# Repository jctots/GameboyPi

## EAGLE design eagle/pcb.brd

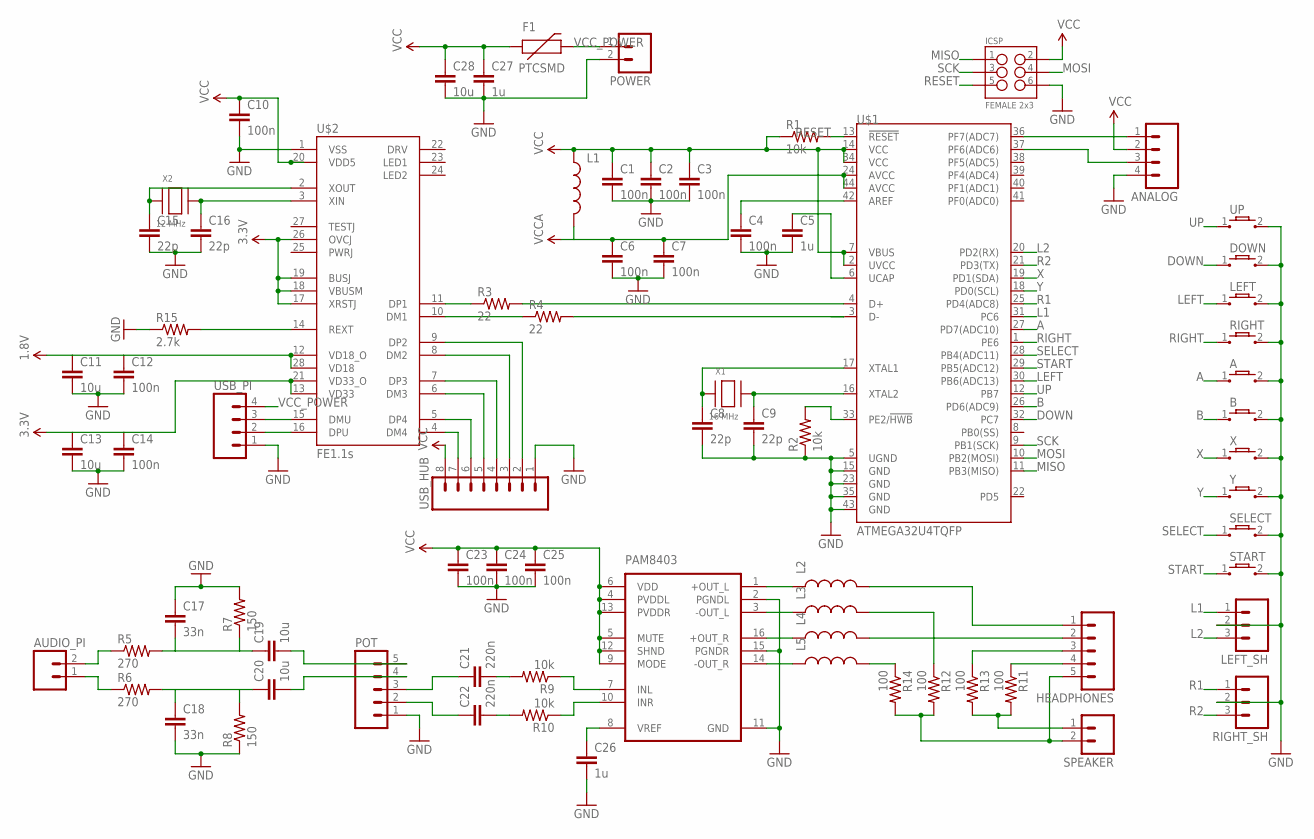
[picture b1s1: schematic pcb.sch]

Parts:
A: DMG_CONDUCTIVE; CIRCLE_BUTTON2
ANALOG: M04PTH; 1X04
AUDIO_PI: M02PTH; 1X02
B: DMG_CONDUCTIVE; CIRCLE_BUTTON2
C1, C2, C3, C4, C6, C7, C10, C12, C14, C23, C24, C25: 100n; 0805
C5, C26, C27: 1u; 0805
C8, C9, C15, C16: 22p; 0805
C11, C13, C19, C20, C28: 10u; 0805
C17, C18: 33n; 0805
C21, C22: 220n; 0805
DOWN: DMG_CONDUCTIVE; CIRCLE_BUTTON2
F1: PTCSMD; PTC-1206
HEADPHONES: M05PTH; 1X05
ICSP: FEMALE 2x3; 2X3
L1, L2, L3, L4, L5: INDUCTOR0805; 0805
LEFT: DMG_CONDUCTIVE; CIRCLE_BUTTON2
LEFT_SH: M03PTH; 1X03
PAM8403: PAM8403; SOP-16
POT: M05PTH; 1X05
POWER: M02PTH; 1X02
R1, R2, R9, R10: 10k; 0805
R3, R4: 22; 0805
R5, R6: 270; 0805
R7, R8: 150; 0805
R11, R12, R13, R14: 100; 0805
R15: 2.7k; 0805
RIGHT: DMG_CONDUCTIVE; CIRCLE_BUTTON2
RIGHT_SH: M03PTH; 1X03
SELECT: DMG_CONDUCTIVE2; START_STOP2
SPEAKER: M02PTH; 1X02
START: DMG_CONDUCTIVE2; START_STOP2
U$1: ATMEGA32U4TQFP; SPARKFUN-DIGITALIC_TQFP44
U$2: FE1.1S; FE1.1S_SSOP-28
UP: DMG_CONDUCTIVE; CIRCLE_BUTTON2
USB_HUB: M08; 1X08_ROUND
USB_PI: M04PTH; 1X04
X: DMG_CONDUCTIVE; CIRCLE_BUTTON2
X1: 16 MHz; NX5032
X2: 12 MHz; NX5032
Y: DMG_CONDUCTIVE; CIRCLE_BUTTON2

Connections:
1.8V: C11.1, C12.1, U$2.12 (VD18_O), U$2.28 (VD18)
3.3V: C13.1, C14.1, U$2.13 (VD33), U$2.17 (XRSTJ), U$2.18 (VBUSM), U$2.19 (BUSJ), U$2.21 (VD33_O), U$2.26 (OVCJ)
A: A.1, U$1.27 (PD7(ADC10))
AUDIO_GND: HEADPHONES.5, R12.2, R14.2, SPEAKER.2
AUDIO_L2MONO: HEADPHONES.4, R11.1
AUDIO_MONO: R11.2, R13.2, SPEAKER.1
AUDIO_R2MONO: HEADPHONES.3, R13.1
AUDIO_STEREO_L: HEADPHONES.1, L2.2
AUDIO_STEREO_R: HEADPHONES.2, L4.2
B: B.1, U$1.26 (PD6(ADC9))
DOWN: DOWN.1, U$1.32 (PC7)
GND: A.2, ANALOG.4, B.2, C1.2, C2.2, C3.2, C4.2, C5.2, C6.2, C7.2, C8.2, C9.2, C10.2, C11.2, C12.2, C13.2, C14.2, C15.2, C16.2, C17.1, C18.2, C23.2, C24.2, C25.2, C26.2, C27.2, C28.2, DOWN.2, ICSP.6, LEFT.2, LEFT_SH.2, PAM8403.2 (PGNDL), PAM8403.11 (GND), PAM8403.15 (PGNDR), POT.1, POWER.2, R2.1, R7.2, R8.1, R15.1, RIGHT.2, RIGHT_SH.2, SELECT.2, START.2, U$1.5 (UGND), U$1.15 (GND), U$1.23 (GND), U$1.35 (GND), U$1.43 (GND), U$2.1 (VSS), UP.2, USB_HUB.1, USB_PI.1, X.2, Y.2
L1: LEFT_SH.1, U$1.31 (PC6)
L2: LEFT_SH.3, U$1.20 (PD2(RX))
LEFT: LEFT.1, U$1.30 (PB6(ADC13))
MISO: ICSP.1, U$1.11 (PB3(MISO))
MOSI: ICSP.4, U$1.10 (PB2(MOSI))
unnamed: C4.1, U$1.42 (AREF)
unnamed: C5.1, U$1.6 (UCAP)
unnamed: R2.2, U$1.33 (PE2/!HWB)
unnamed: R3.1, U$2.11 (DP1)
unnamed: R4.1, U$2.10 (DM1)
unnamed: C8.1, U$1.17 (XTAL1), X1.P$1
unnamed: C9.1, U$1.16 (XTAL2), X1.P$2
unnamed: R3.2, U$1.4 (D+)
unnamed: R4.2, U$1.3 (D-)
unnamed: C15.1, U$2.2 (XOUT), X2.P$1
unnamed: C16.1, U$2.3 (XIN), X2.P$2
unnamed: AUDIO_PI.2, R5.1
unnamed: AUDIO_PI.1, R6.1
unnamed: C17.2, C19.1, R5.2, R7.1
unnamed: C18.1, C20.1, R6.2, R8.2
unnamed: C26.1, PAM8403.8 (VREF)
unnamed: L2.1, PAM8403.1 (+OUT_L)
unnamed: C19.2, POT.5
unnamed: C20.2, POT.4
unnamed: C21.1, POT.3
unnamed: C22.1, POT.2
unnamed: C21.2, R9.2
unnamed: C22.2, R10.2
unnamed: PAM8403.7 (INL), R9.1
unnamed: PAM8403.10 (INR), R10.1
unnamed: L3.1, PAM8403.3 (-OUT_L)
unnamed: L3.2, R12.1
unnamed: L4.1, PAM8403.16 (+OUT_R)
unnamed: L5.1, PAM8403.14 (-OUT_R)
unnamed: L5.2, R14.1
unnamed: U$2.4 (DM4), USB_HUB.7
unnamed: U$2.5 (DP4), USB_HUB.6
unnamed: U$2.6 (DM3), USB_HUB.5
unnamed: R15.2, U$2.14 (REXT)
unnamed: U$2.7 (DP3), USB_HUB.4
unnamed: U$2.8 (DM2), USB_HUB.3
unnamed: ANALOG.1, U$1.36 (PF7(ADC7))
unnamed: ANALOG.3, U$1.37 (PF6(ADC6))
unnamed: U$2.9 (DP2), USB_HUB.2
unnamed: U$2.15 (DMU), USB_PI.3
unnamed: U$2.16 (DPU), USB_PI.2
R1: RIGHT_SH.1, U$1.25 (PD4(ADC8))
R2: RIGHT_SH.3, U$1.21 (PD3(TX))
RESET: ICSP.5, R1.2, U$1.13 (!RESET)
RIGHT: RIGHT.1, U$1.1 (PE6)
SCK: ICSP.3, U$1.9 (PB1(SCK))
SELECT: SELECT.1, U$1.28 (PB4(ADC11))
START: START.1, U$1.29 (PB5(ADC12))
UP: U$1.12 (PB7), UP.1
VCC: ANALOG.2, C1.1, C2.1, C3.1, C10.1, C23.1, C24.1, C25.1, C27.1, C28.1, F1.1, ICSP.2, L1.1, PAM8403.4 (PVDDL), PAM8403.5 (MUTE), PAM8403.6 (VDD), PAM8403.9 (MODE), PAM8403.12 (SHND), PAM8403.13 (PVDDR), R1.1, U$1.2 (UVCC), U$1.7 (VBUS), U$1.14 (VCC), U$1.34 (VCC), U$2.20 (VDD5), USB_HUB.8
VCCA: C6.1, C7.1, L1.2, U$1.24 (AVCC), U$1.44 (AVCC)
VCC_POWER: F1.2, POWER.1, USB_PI.4
X: U$1.19 (PD1(SDA)), X.1
Y: U$1.18 (PD0(SCL)), Y.1

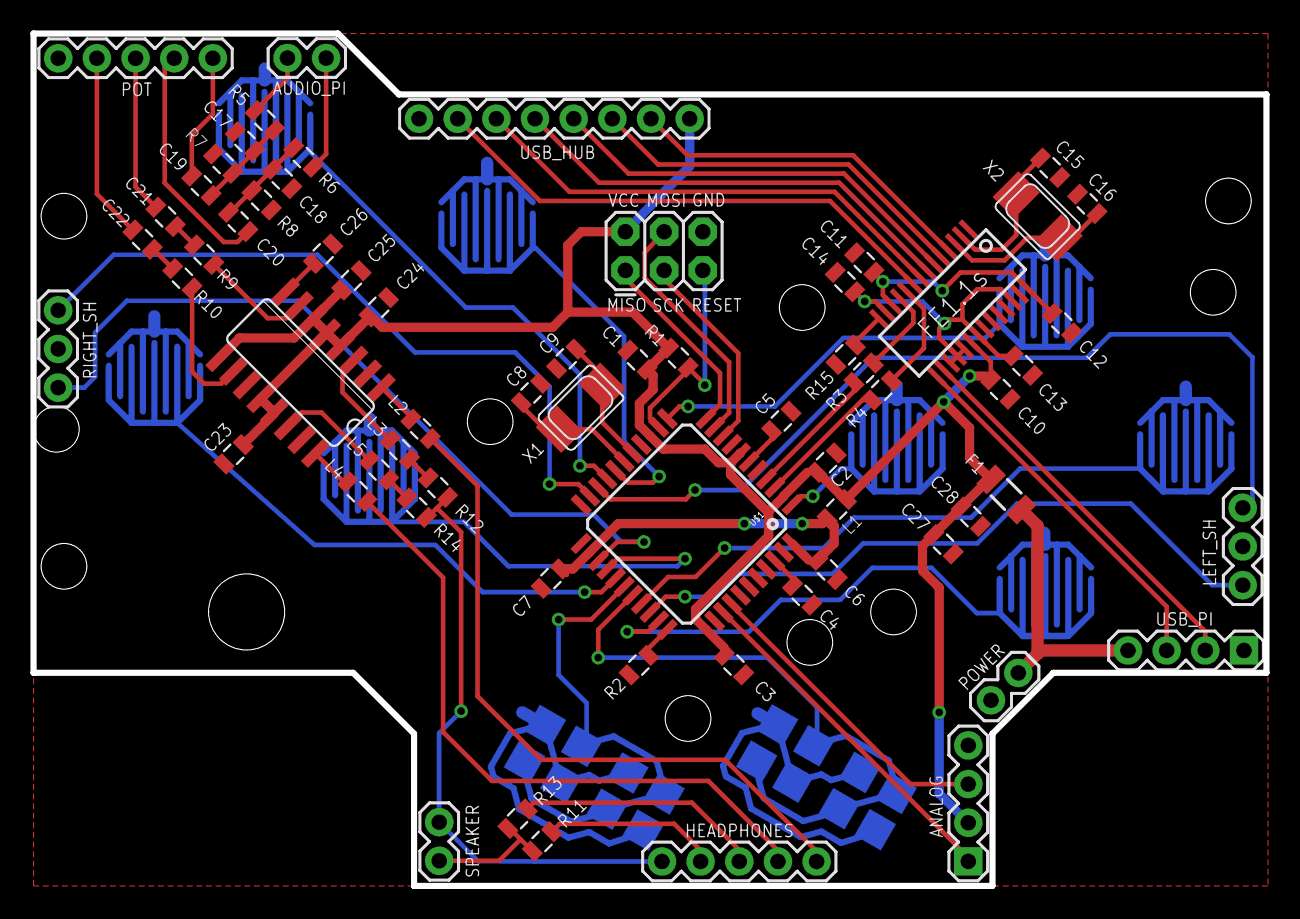
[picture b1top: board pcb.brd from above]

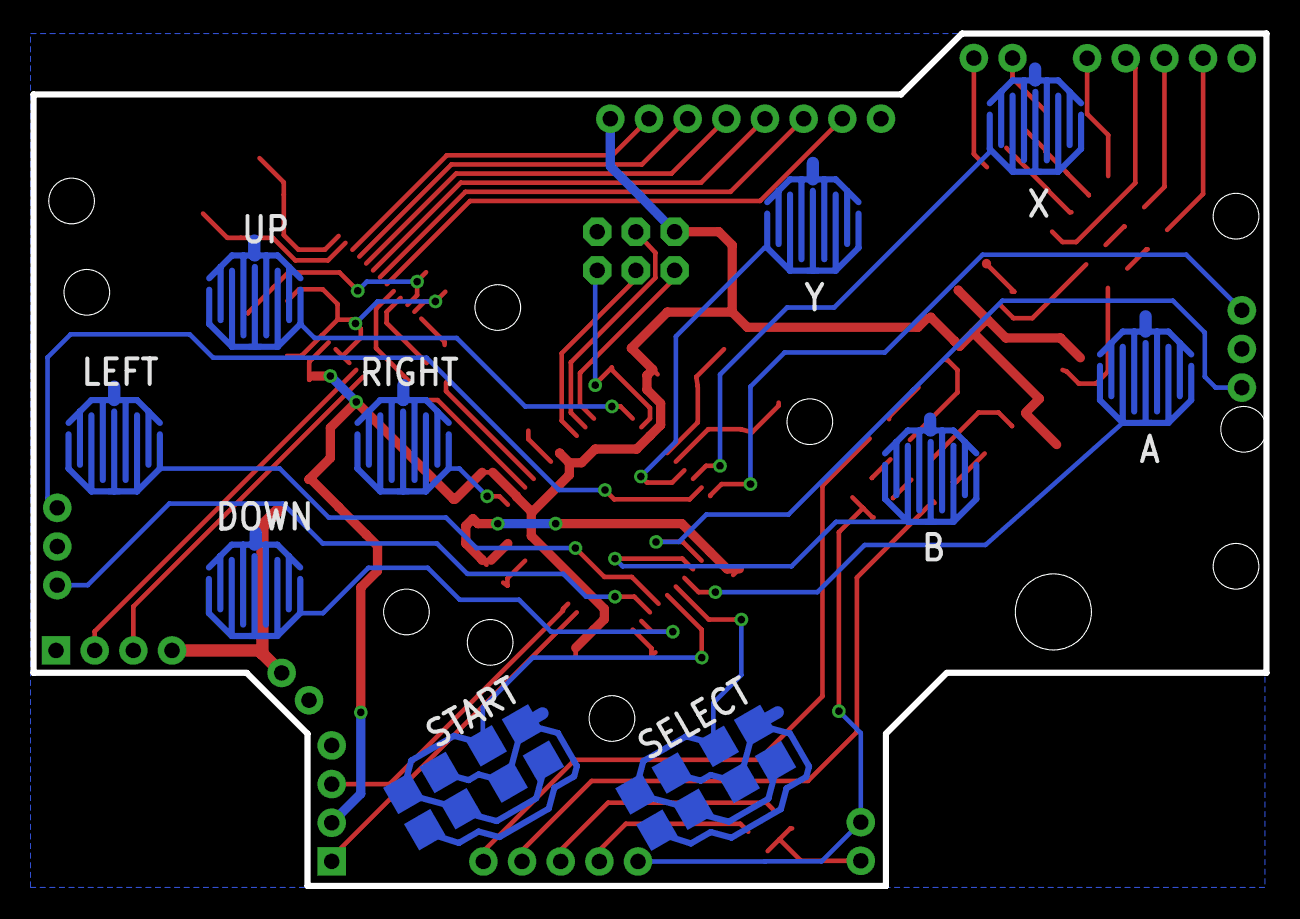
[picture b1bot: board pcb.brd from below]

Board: 2 copper layers, 81.0 x 56.0 mm, 75 parts (10 on the bottom side), 71 nets.

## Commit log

2016-10-16 upload own modified libs
2016-10-16 top layer almost done, continue with bottom layer
2016-10-16 added gitignore
2016-10-17 completed routing top and bottom
2016-10-18 finished v0.2 and gerber files
2016-10-19 v0.3, moved the left shoulder away from rpi zero

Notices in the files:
parts and their libraries:
SparkFun-Passives: Licensing: Creative Commons ShareAlike 4.0 International - https://creativecommons.org/licenses/by-sa/4.0
